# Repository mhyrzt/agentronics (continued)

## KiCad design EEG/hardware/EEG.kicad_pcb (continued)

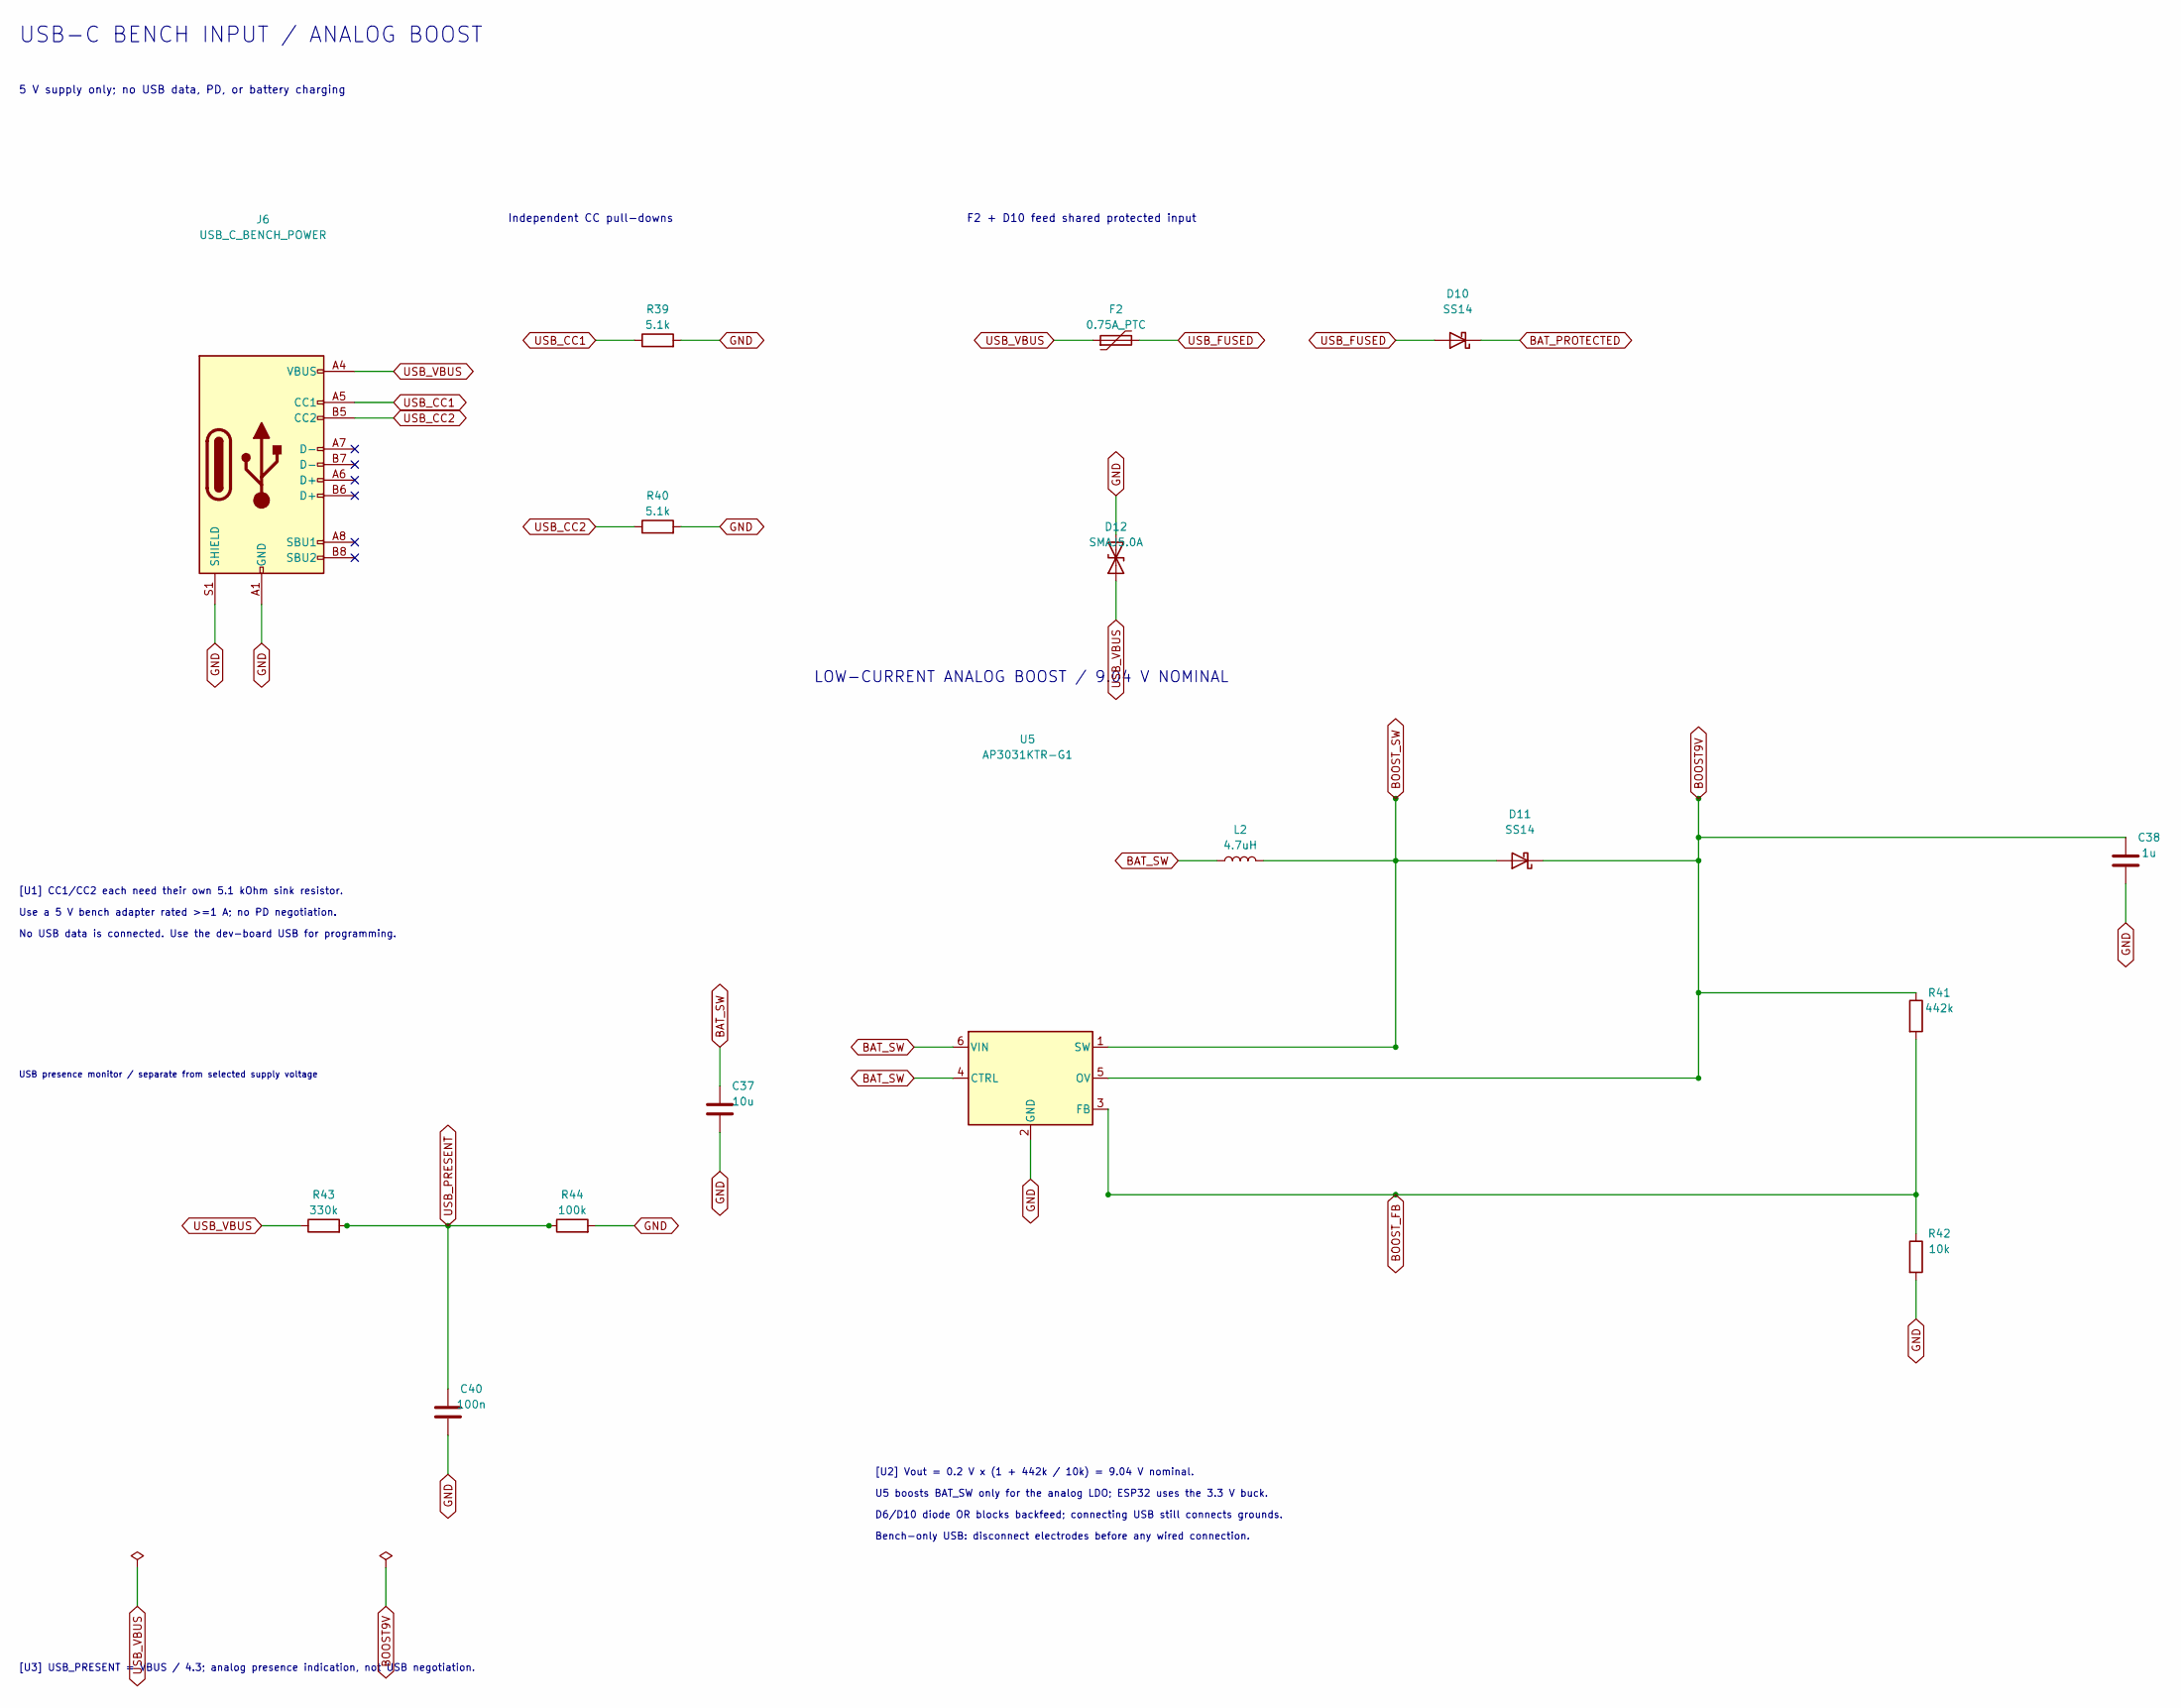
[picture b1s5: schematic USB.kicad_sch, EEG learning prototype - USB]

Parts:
C37: 10u; C_1206_3216Metric; MPN GRM31CR71C106KA12L
C38: 1u; C_0805_2012Metric; MPN GRM21BR71E105KA99L
C40: 100n; C_0805_2012Metric; MPN GRM21BR71H104KA01L
D10, D11: SS14; D_SMA; MPN SS14
D12: SMAJ5.0A; D_SMA; MPN SMAJ5.0A
F2: 0.75A_PTC; Fuse_1812_4532Metric; MPN 1812L075/24DR
J6: USB_C_BENCH_POWER; USB_C_Receptacle_GCT_USB4105-xx-A_16P_TopMnt_Horizontal; MPN USB4105-GF-A
L2: 4.7uH; L_Bourns_SRP5030T; MPN SRP5030T-4R7M
R39, R40: 5.1k; R_0805_2012Metric; MPN RC0805FR-075K1L
R41: 442k; R_0805_2012Metric; MPN RC0805FR-07442KL
R42: 10k; R_0805_2012Metric; MPN RC0805FR-0710KL
R43: 330k; R_0805_2012Metric; MPN RC0805FR-07330KL
R44: 100k; R_0805_2012Metric; MPN RC0805FR-07100KL
U5: AP3031KTR-G1; SOT-23-6; MPN AP3031KTR-G1

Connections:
BAT_PROTECTED: D10.1 (K); also elsewhere on the board
BAT_SW: C37.1, L2.1, U5.4 (CTRL), U5.6 (VIN); also elsewhere on the board
BOOST9V: C38.1, D11.1 (K), R41.1, U5.5 (OV); also elsewhere on the board
BOOST_FB: R41.2, R42.1, U5.3 (FB)
BOOST_SW: D11.2 (A), L2.2, U5.1 (SW)
GND: C37.2, C38.2, C40.2, D12.2 (A2), J6.A1 (GND), J6.A12 (GND), J6.B1 (GND), J6.B12 (GND), J6.S1 (SHIELD), R39.2, R40.2, R42.2, R44.2, U5.2 (GND); also elsewhere on the board
USB_CC1: J6.A5 (CC1), R39.1
USB_CC2: J6.B5 (CC2), R40.1
USB_FUSED: D10.2 (A), F2.2
USB_PRESENT: C40.1, R43.2, R44.1; also elsewhere on the board
USB_VBUS: D12.1 (A1), F2.1, J6.A4 (VBUS), J6.A9 (VBUS), J6.B4 (VBUS), J6.B9 (VBUS), R43.1

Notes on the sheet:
USB-C BENCH INPUT / ANALOG BOOST
5 V supply only; no USB data, PD, or battery charging
Independent CC pull-downs
F2 + D10 feed shared protected input
LOW-CURRENT ANALOG BOOST / 9.04 V NOMINAL
USB presence monitor / separate from selected supply voltage
[U1] CC1/CC2 each need their own 5.1 kOhm sink resistor.
Use a 5 V bench adapter rated >=1 A; no PD negotiation.
No USB data is connected. Use the dev-board USB for programming.
[U2] Vout = 0.2 V x (1 + 442k / 10k) = 9.04 V nominal.
U5 boosts BAT_SW only for the analog LDO; ESP32 uses the 3.3 V buck.
D6/D10 diode OR blocks backfeed; connecting USB still connects grounds.
Bench-only USB: disconnect electrodes before any wired connection.
[U3] USB_PRESENT = VBUS / 4.3; analog presence indication, not USB negotiation.

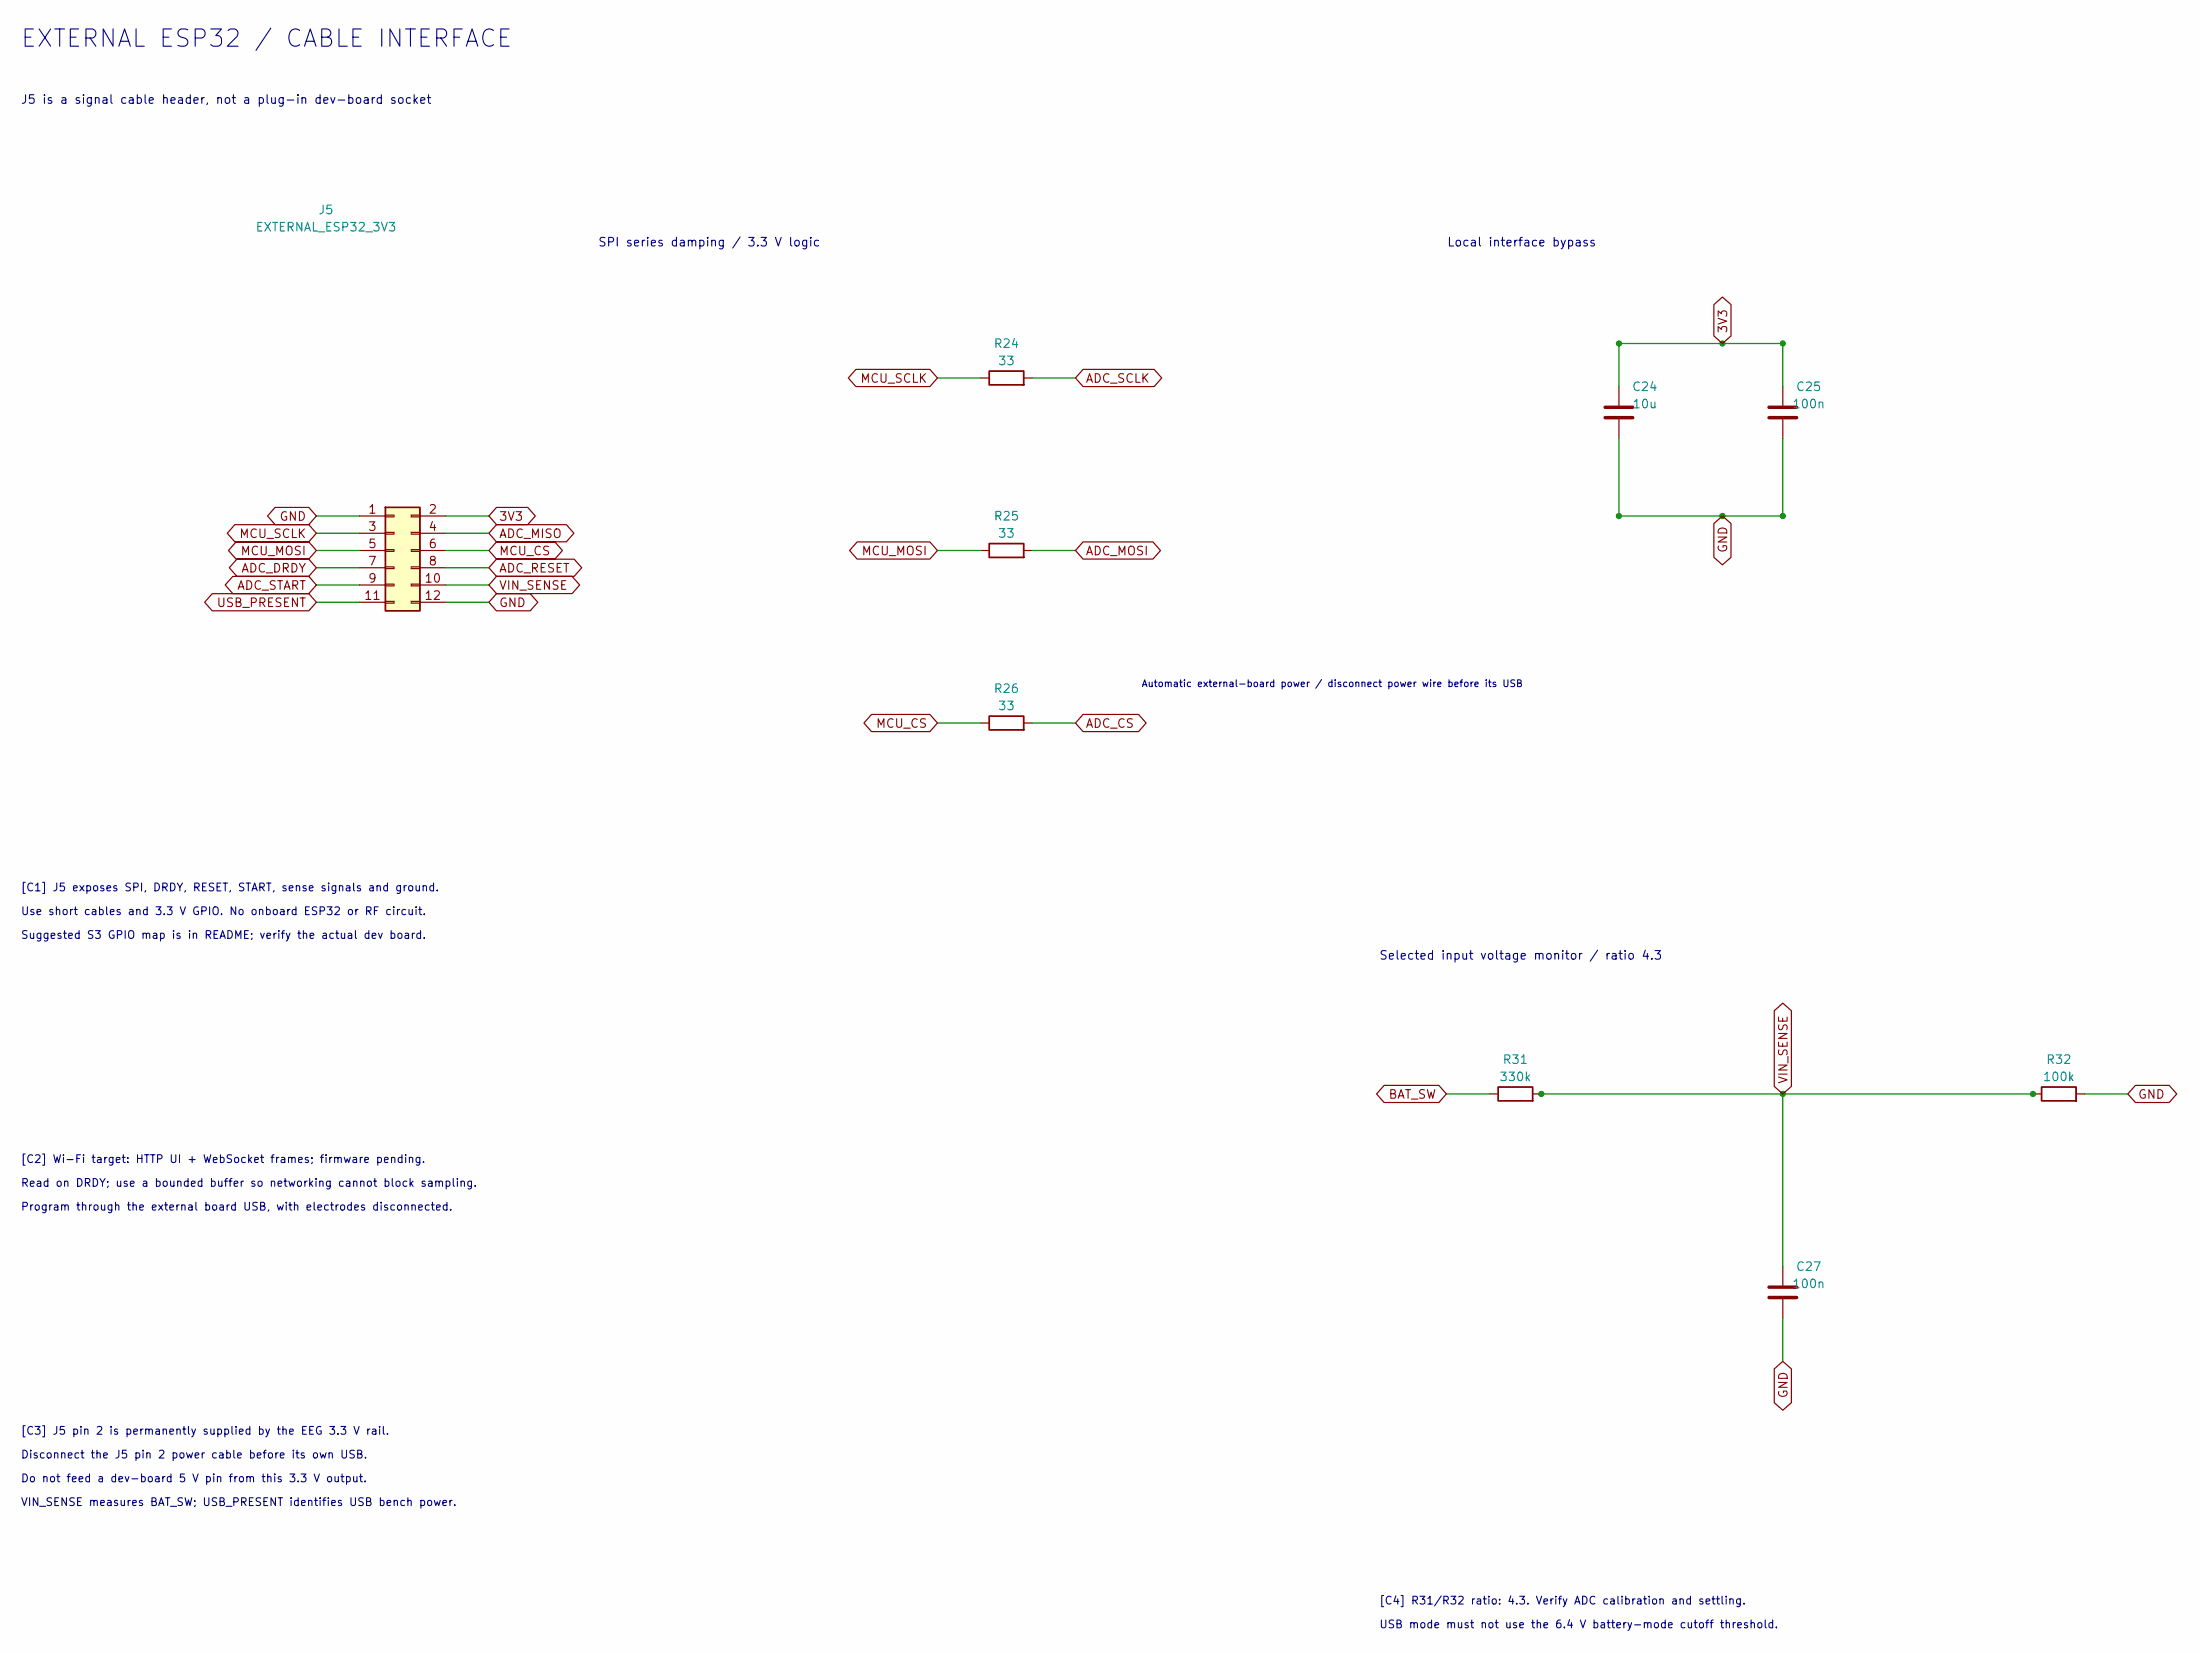
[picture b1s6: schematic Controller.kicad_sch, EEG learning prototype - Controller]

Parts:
C24: 10u; C_1206_3216Metric; MPN GRM31CR71C106KA12L
C25, C27: 100n; C_0805_2012Metric; MPN GRM21BR71H104KA01L
J5: EXTERNAL_ESP32_3V3; PinHeader_2x06_P2.54mm_Vertical; MPN 61301221121
R24, R25, R26: 33; R_0805_2012Metric; MPN RC0805FR-0733RL
R31: 330k; R_0805_2012Metric; MPN RC0805FR-07330KL
R32: 100k; R_0805_2012Metric; MPN RC0805FR-07100KL

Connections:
3V3: C24.1, C25.1, J5.2; also elsewhere on the board
ADC_CS: R26.2; also elsewhere on the board
ADC_DRDY: J5.7; also elsewhere on the board
ADC_MISO: J5.4; also elsewhere on the board
ADC_MOSI: R25.2; also elsewhere on the board
ADC_RESET: J5.8; also elsewhere on the board
ADC_SCLK: R24.2; also elsewhere on the board
ADC_START: J5.9; also elsewhere on the board
BAT_SW: R31.1; also elsewhere on the board
GND: C24.2, C25.2, C27.2, J5.1, J5.12, R32.2; also elsewhere on the board
MCU_CS: J5.6, R26.1
MCU_MOSI: J5.5, R25.1
MCU_SCLK: J5.3, R24.1
USB_PRESENT: J5.11; also elsewhere on the board
VIN_SENSE: C27.1, J5.10, R31.2, R32.1

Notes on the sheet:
EXTERNAL ESP32 / CABLE INTERFACE
J5 is a signal cable header, not a plug-in dev-board socket
SPI series damping / 3.3 V logic
Local interface bypass
Automatic external-board power / disconnect power wire before its USB
Selected input voltage monitor / ratio 4.3
[C1] J5 exposes SPI, DRDY, RESET, START, sense signals and ground.
Use short cables and 3.3 V GPIO. No onboard ESP32 or RF circuit.
Suggested S3 GPIO map is in README; verify the actual dev board.
[C2] Wi-Fi target: HTTP UI + WebSocket frames; firmware pending.
Read on DRDY; use a bounded buffer so networking cannot block sampling.
Program through the external board USB, with electrodes disconnected.
[C3] J5 pin 2 is permanently supplied by the EEG 3.3 V rail.
Disconnect the J5 pin 2 power cable before its own USB.
Do not feed a dev-board 5 V pin from this 3.3 V output.
VIN_SENSE measures BAT_SW; USB_PRESENT identifies USB bench power.
[C4] R31/R32 ratio: 4.3. Verify ADC calibration and settling.
USB mode must not use the 6.4 V battery-mode cutoff threshold.

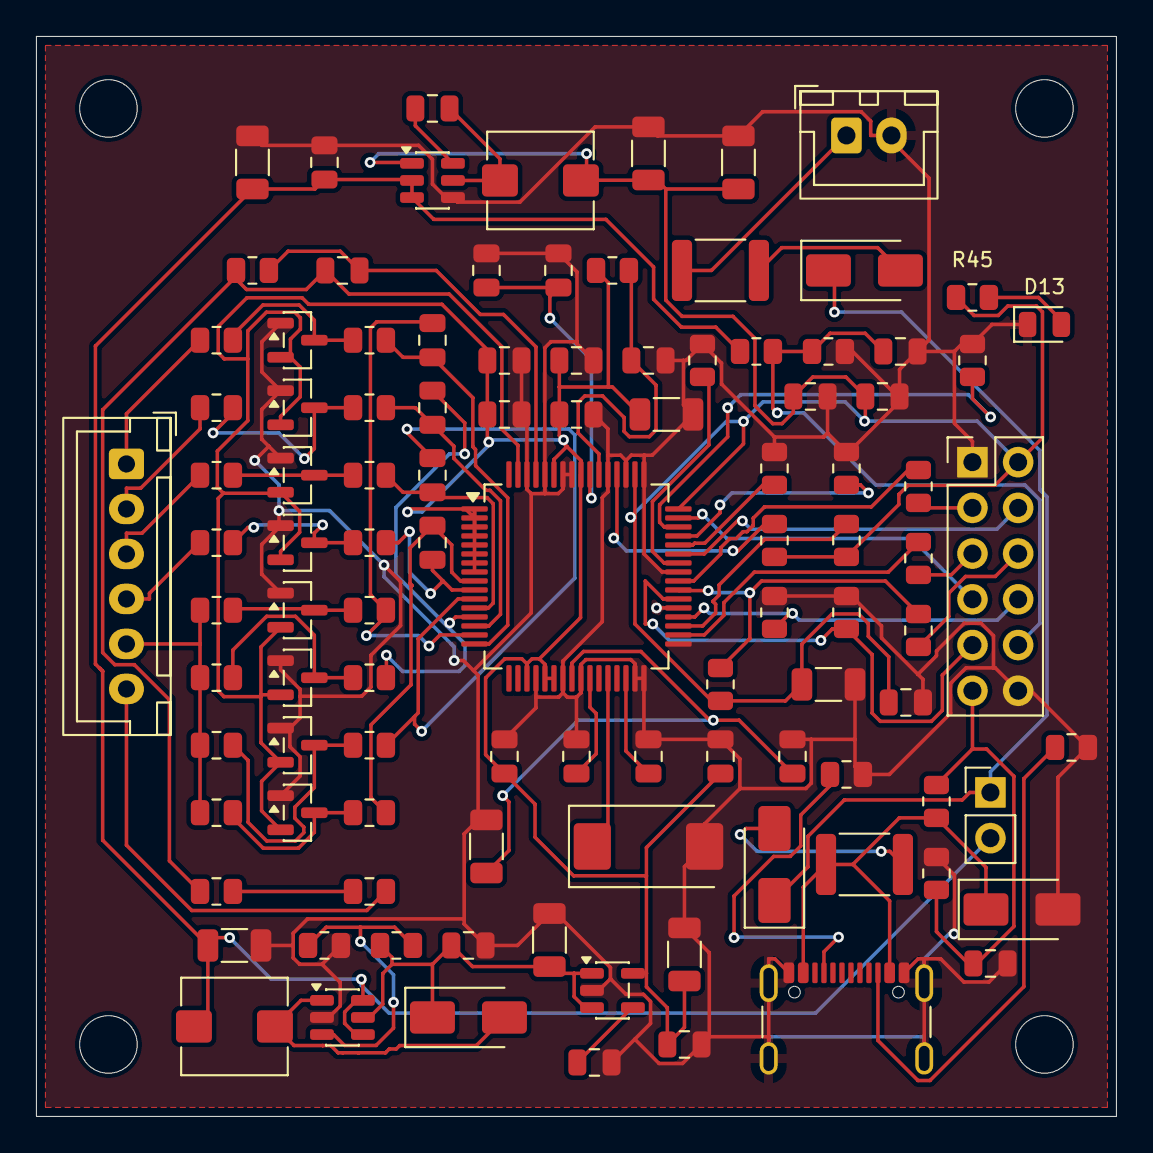
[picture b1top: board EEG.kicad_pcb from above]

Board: 2 copper layers, 60.0 x 60.0 mm, 108 parts (0 on the bottom side), 67 nets.

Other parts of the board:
MH1, MH2, MH3, MH4: MountingHole_3.2mm; MountingHole_3.2mm_M3

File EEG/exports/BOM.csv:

"References","Value","Footprint","MPN","Manufacturer","Quantity","Notes"
"C1-C4","4.7n","Capacitor_SMD:C_0805_2012Metric","GRM21A5C1H472JA01D","Murata","4","C0G differential RF filter, 50V, 5%"
"C5","1n","Capacitor_SMD:C_0805_2012Metric","GRM21A5C1H102JA01D","Murata","1","C0G bias feedback; bench stability verification required"
"C6","100u","Capacitor_Tantalum_SMD:CP_EIA-7343-31_Kemet-D","T491D107K010AT","KEMET","1","Tantalum 100uF 10V; polarity positive at VCAP1"
"C7,C8,C10,C13-C18,C21,C23","1u","Capacitor_SMD:C_0805_2012Metric","GRM21BR71E105KA99L","Murata","11","Local bypass; voltage >=16V; verify effective capacitance,MCU reset delay,Place one beside each AVDD supply group"
"C9,C12,C20,C22,C25,C27,C29,C30,C36","100n","Capacitor_SMD:C_0805_2012Metric","GRM21BR71H104KA01L","Murata","9","Bootstrap,Local bypass; voltage >=16V; verify effective capacitance"
"C11,C19,C24,C28,C33,C35","10u","Capacitor_SMD:C_1206_3216Metric","GRM31CR71C106KA12L","Murata","6","Analog input bypass,Analog rail bulk bypass,Ensure effective capacitance >=2.2uF and stability ESR,Input ceramic 16V minimum,Local bulk bypass,Local bypass; voltage >=16V; verify effective capacitance"
"C26,C31,C32","22u","Capacitor_SMD:C_1206_3216Metric","GRM31CR61E226KE15L","Murata","3","Buck output 25V X5R,Radio transient reserve"
"C34","10n","Capacitor_SMD:C_0805_2012Metric","GRM21A5C1H103JA01D","Murata","1","C0G low noise bypass"
"D1-D5,D7-D9","BAV199","Package_TO_SOT_SMD:SOT-23","BAV199,215","Nexperia","8","Low leakage rail clamp. Not a certified ESD or defibrillator protection circuit."
"D6","SS14","Diode_SMD:D_SMA","SS14","Diodes Incorporated","1","Reverse polarity blocking"
"F1","0.75A_PTC","Fuse:Fuse_1812_4532Metric","1812L075/24DR","Littelfuse","1","Pack also requires its own protection and fuse"
"J1","ELECTRODES","Connector_JST:JST_XH_B6B-XH-A_1x06_P2.50mm_Vertical","B6B-XH-A","JST","1","Electrode connector: channels 1-4, reference, bias. No ground electrode."
"J2","2S_BATTERY","Connector_JST:JST_XH_B2B-XH-A_1x02_P2.50mm_Vertical","B2B-XH-A","JST","1","Protected 2S Li-ion pack, 6.4-8.4V operating. Remove pack for external charging."
"J3","UART_BENCH_ONLY","Connector_PinHeader_2.54mm:PinHeader_1x06_P2.54mm_Vertical","61300611121","Wurth Elektronik","1","3V3 pin is a sense output: do not supply external power. Disconnect all electrodes before attaching programmer."
"J4","POWER_ENABLE","Connector_PinHeader_2.54mm:PinHeader_1x02_P2.54mm_Vertical","61300211121","Wurth Elektronik","1","Fit a rated 2.54mm shunt to enable power; remove to turn off. Battery disconnect is the master power switch."
"L1","4.7uH","Inductor_SMD:L_Bourns_SRP5030T","SRP5030T-4R7M","Bourns","1","Shielded 4.7uH, 4.6A RMS, 6A saturation per Bourns datasheet"
"R1-R10,R19,R20,R23,R27-R30,R33-R38","10k","Resistor_SMD:R_0805_2012Metric","RC0805FR-0710KL","Yageo","23","Input series protection; 1%, 0805,SPI deselect while MCU resets,Secondary current limiting and differential RC filter"
"R11,R12","499k","Resistor_SMD:R_0805_2012Metric","RC0805FR-07499KL","Yageo","2","Independent bias current limiting resistor"
"R13","1M","Resistor_SMD:R_0805_2012Metric","RC0805FR-071ML","Yageo","1","Bias feedback"
"R14","0","Resistor_SMD:R_0805_2012Metric","RC0805JR-070RL","Yageo","1","Star link to AVDD1"
"R15-R18,R21,R22,R32","100k","Resistor_SMD:R_0805_2012Metric","RC0805FR-07100KL","Yageo","7","Hold ADC in reset until firmware sequencing,Unused GPIO pulldown"
"R24-R26","33","Resistor_SMD:R_0805_2012Metric","RC0805FR-0733RL","Yageo","3","SPI source termination"
"R31","330k","Resistor_SMD:R_0805_2012Metric","RC0805FR-07330KL","Yageo","1",""
"SW2","RESET","Button_Switch_SMD:SW_SPST_TL3342","TL3342F160QG","E-Switch","1",""
"SW3","BOOT","Button_Switch_SMD:SW_SPST_TL3342","TL3342F160QG","E-Switch","1",""
"U1","ADS1299-4","Package_QFP:TQFP-64_10x10mm_P0.5mm","ADS1299-4PAG","Texas Instruments","1","4-channel ADS1299-4 variant. Independent differential filters; SRB1/SRB2 disabled. Internal bias reference."
"U2","ESP32-C3-WROOM-02-N4","EEG_Footprints:ESP32-C3-WROOM-02_EdgeAntenna","ESP32-C3-WROOM-02-N4","Espressif","1","BLE data; antenna beyond board edge; wired programming only with electrodes disconnected."
"U3","AP63203WU-7","Package_TO_SOT_SMD:TSOT-23-6","AP63203WU-7","Diodes Incorporated","1",""
"U4","LP2985AIM5-5.0/NOPB","Package_TO_SOT_SMD:SOT-23-5","LP2985AIM5-5.0/NOPB","Texas Instruments","1","5V analog regulator; bypass 10nF; effective output capacitance >=2.2uF"

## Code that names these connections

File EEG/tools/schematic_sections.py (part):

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        title('REFERENCE / VCAP BYPASS',190,45,1.8)
        title('Follow TI placement guidance; C6 polarity matters',190,53,1.0)
        title('Bias amplifier feedback',330,119,1.27)
        for net,pin,x,angle in (('BIAS_OUT',1,335,180),('BIAS_INV',2,365,0)):
            x=grid(x);a=point(('R13',pin));b=point(('C5',pin))
            path([a,(x,a[1]),(x,b[1]),b]);handled.update({('R13',str(pin)),('C5',str(pin))})
            label(net,(x,grid(150)),angle)
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        group('BAT_FUSED',[('F1',2),('D6',2)],'y',y,(grid(108),y),270)
        group('BAT_PROTECTED',[('D6',1),('J4',1)],'y',y,(grid(145),y),270)
        p=point(('J4',2));handled.add(('J4','2'))
        path([p,(grid(165),p[1]),(grid(165),grid(61)),(grid(215),grid(61))]);label('BAT_SW',(grid(215),grid(61)),0)
        title('3.3 V / DIGITAL SUPPLY',25,75,1.8)
        group('BAT_SW',[('C28',1),('C29',1),('U3',3),('U3',2)],'x',120,(grid(120),grid(85)),90)
        group('BUCK_SW',[('U3',5),('C30',2),('L1',1)],'y',90,(grid(175),grid(90)),90)
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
